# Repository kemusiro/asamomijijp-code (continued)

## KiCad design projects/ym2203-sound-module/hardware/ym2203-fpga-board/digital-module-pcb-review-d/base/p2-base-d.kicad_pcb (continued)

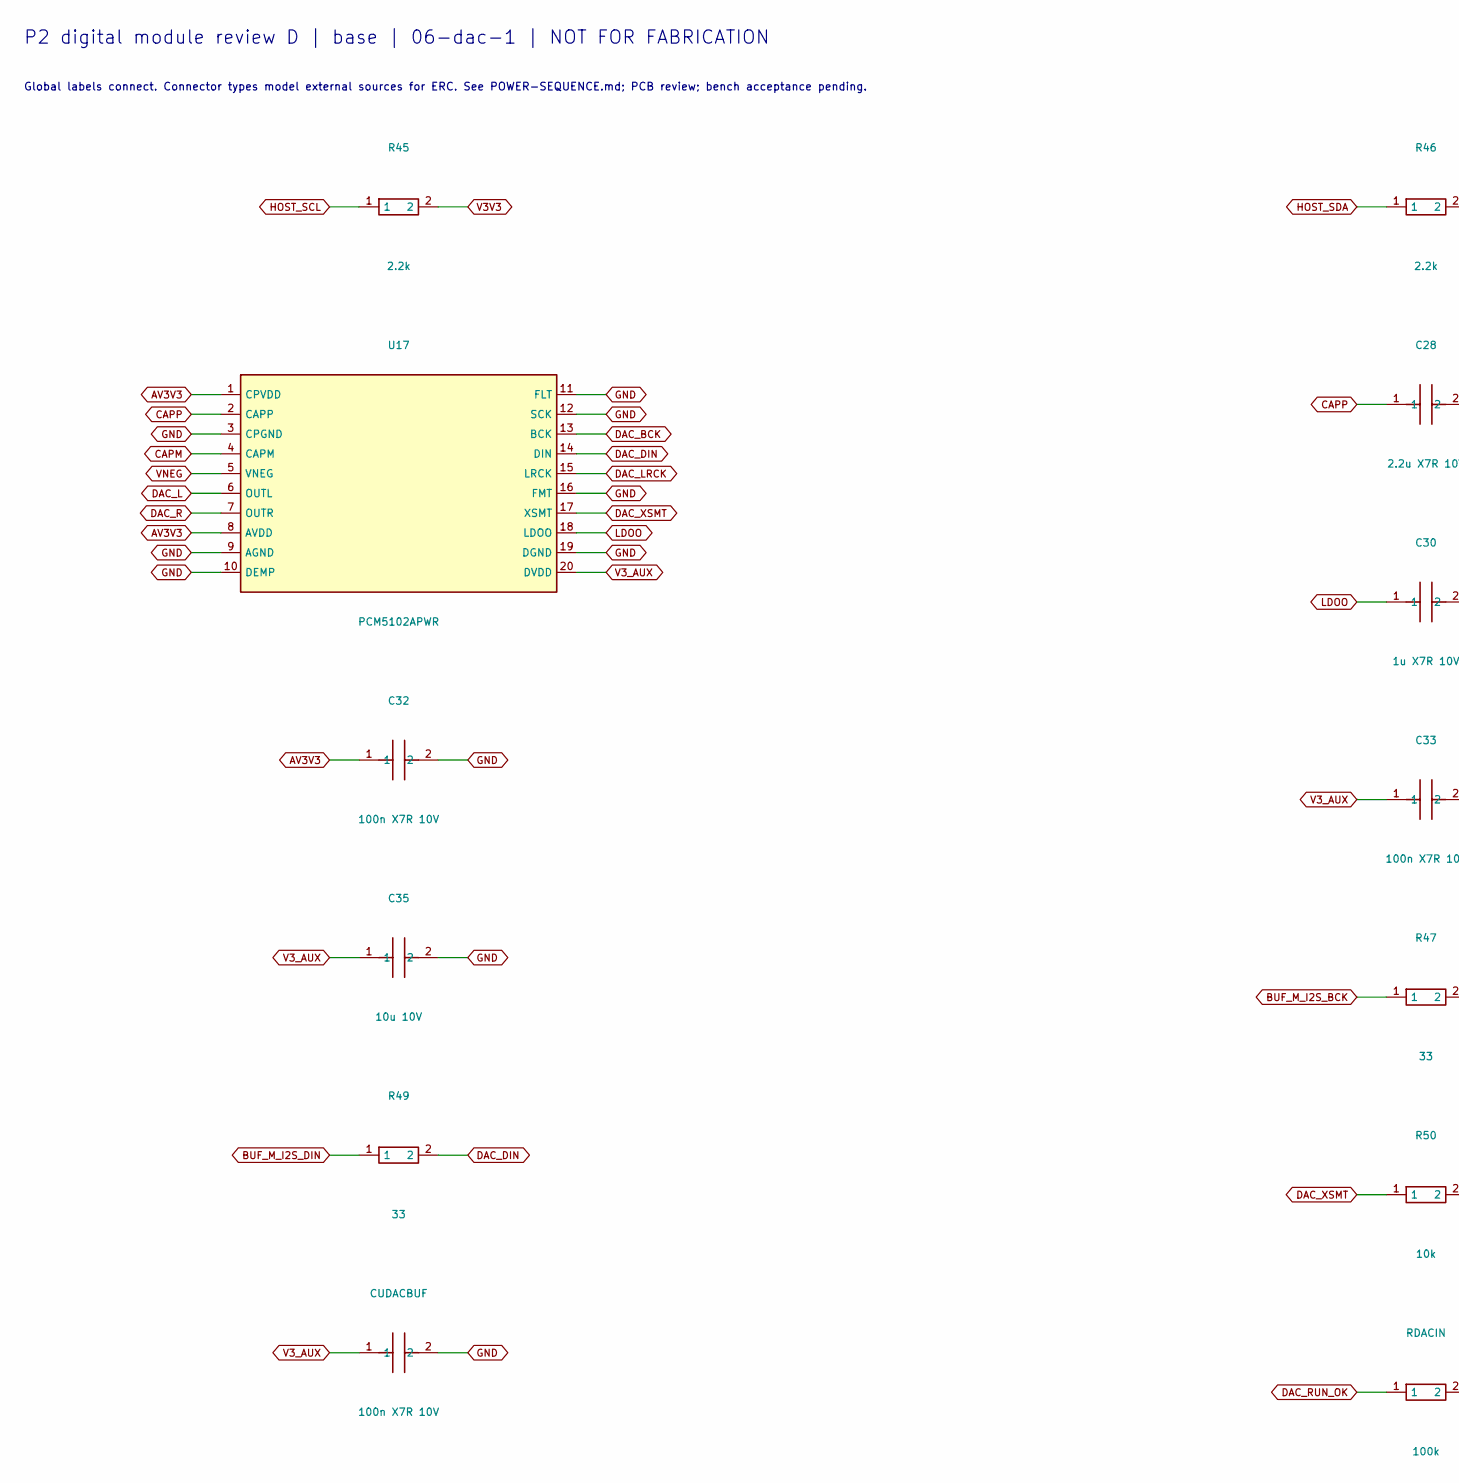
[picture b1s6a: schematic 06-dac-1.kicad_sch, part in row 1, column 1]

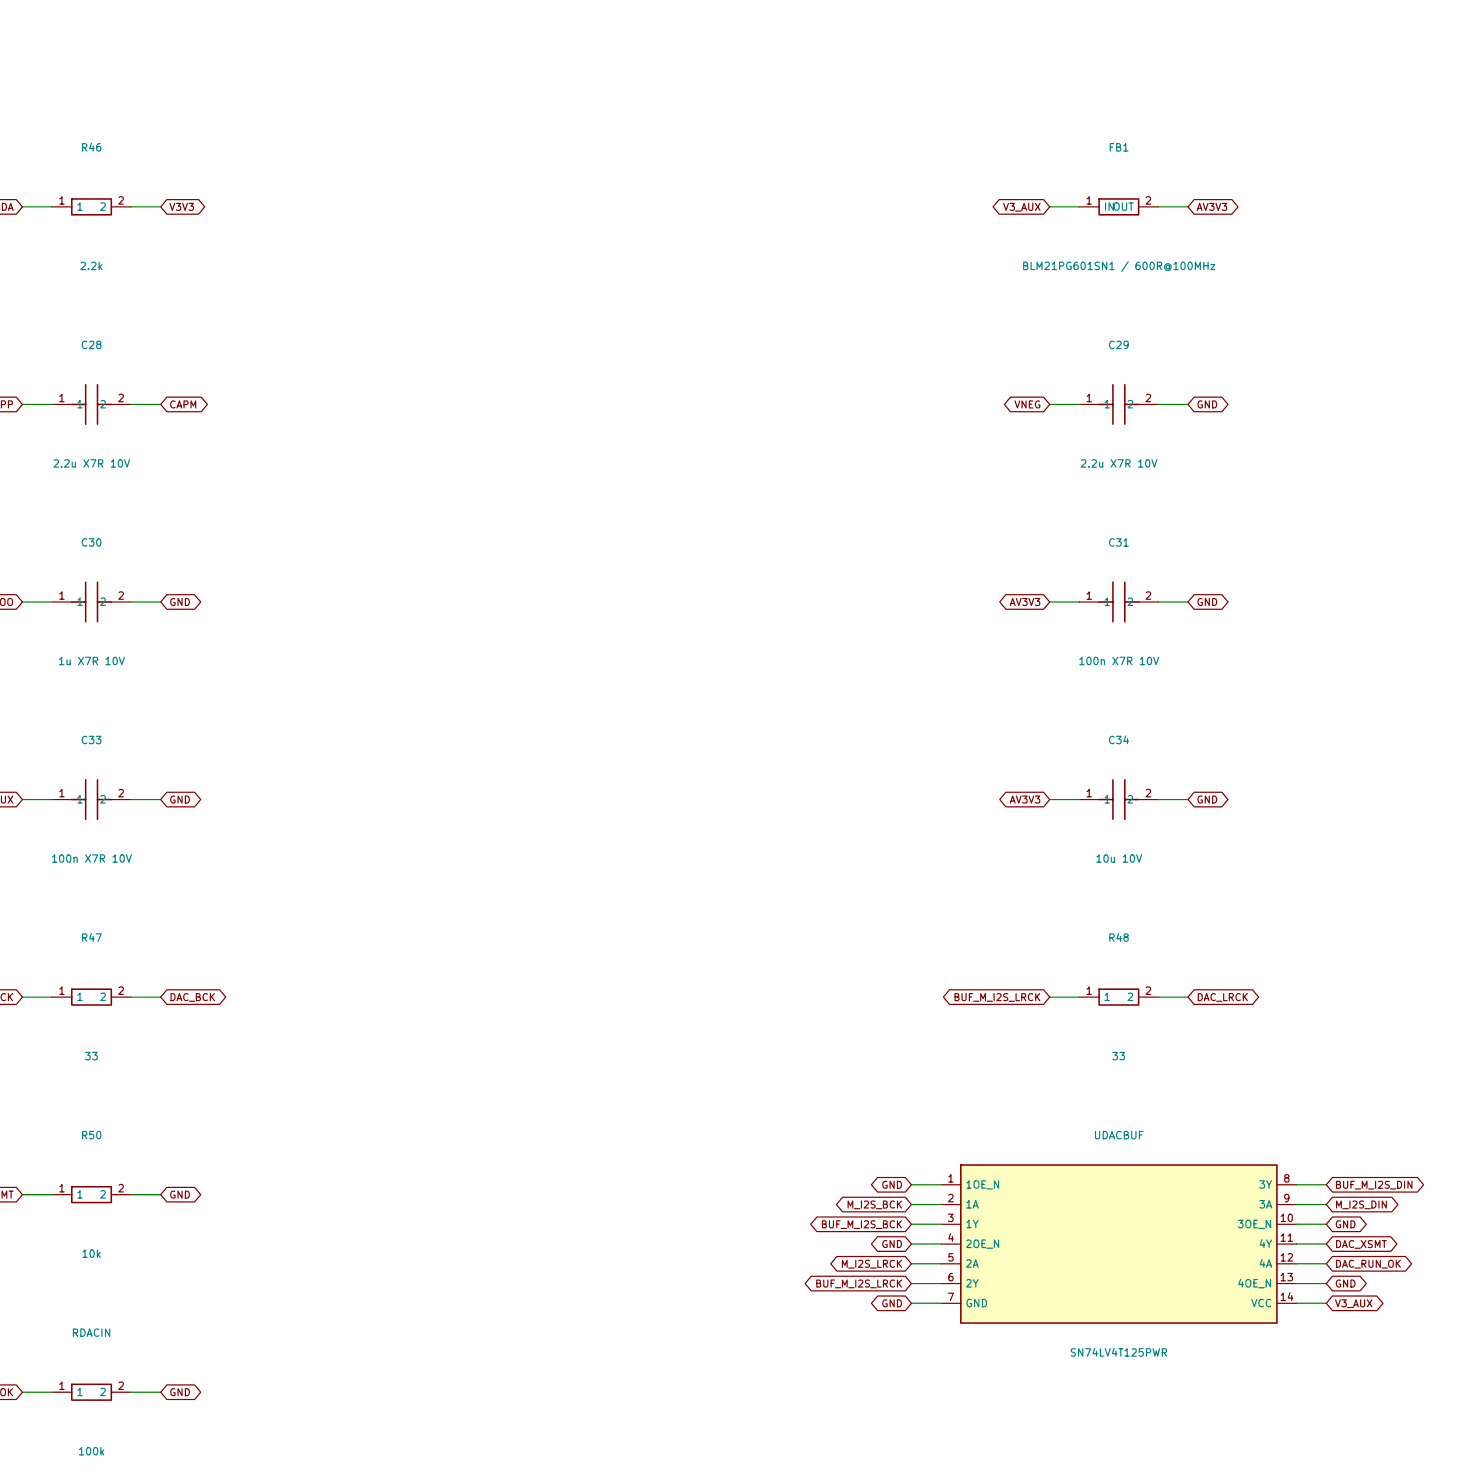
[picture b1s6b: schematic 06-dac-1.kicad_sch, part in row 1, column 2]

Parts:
C28, C29: 2.2u X7R 10V; C_0805_2012Metric
C30: 1u X7R 10V; C_0805_2012Metric
C31, C32, C33: 100n X7R 10V; C_0805_2012Metric
C34, C35: 10u 10V; C_0805_2012Metric
CUDACBUF: 100n X7R 10V; C_0805_2012Metric
FB1: BLM21PG601SN1 / 600R@100MHz; L_0805_2012Metric
R45, R46: 2.2k; R_0805_2012Metric
R47, R48, R49: 33; R_0805_2012Metric
R50: 10k; R_0805_2012Metric
RDACIN: 100k; R_0805_2012Metric
U17: PCM5102APWR; TSSOP-20_4.4x6.5mm_P0.65mm
UDACBUF: SN74LV4T125PWR; TSSOP-14_4.4x5mm_P0.65mm

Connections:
AV3V3: C31.1, C32.1, C34.1, FB1.2 (OUT), U17.1 (CPVDD), U17.8 (AVDD)
BUF_M_I2S_BCK: R47.1, UDACBUF.3 (1Y)
BUF_M_I2S_DIN: R49.1, UDACBUF.8 (3Y)
BUF_M_I2S_LRCK: R48.1, UDACBUF.6 (2Y)
CAPM: C28.2, U17.4 (CAPM)
CAPP: C28.1, U17.2 (CAPP)
DAC_BCK: R47.2, U17.13 (BCK); also elsewhere on the board
DAC_DIN: R49.2, U17.14 (DIN); also elsewhere on the board
DAC_L: U17.6 (OUTL); also elsewhere on the board
DAC_LRCK: R48.2, U17.15 (LRCK); also elsewhere on the board
DAC_R: U17.7 (OUTR); also elsewhere on the board
DAC_RUN_OK: RDACIN.1, UDACBUF.12 (4A); also elsewhere on the board
DAC_XSMT: R50.1, U17.17 (XSMT), UDACBUF.11 (4Y)
GND: C29.2, C30.2, C31.2, C32.2, C33.2, C34.2, C35.2, CUDACBUF.2, R50.2, RDACIN.2, U17.3 (CPGND), U17.9 (AGND), U17.10 (DEMP), U17.11 (FLT), U17.12 (SCK), U17.16 (FMT), U17.19 (DGND), UDACBUF.1 (1OE_N), UDACBUF.4 (2OE_N), UDACBUF.7 (GND), UDACBUF.10 (3OE_N), UDACBUF.13 (4OE_N); also elsewhere on the board
HOST_SCL: R45.1; also elsewhere on the board
HOST_SDA: R46.1; also elsewhere on the board
LDOO: C30.1, U17.18 (LDOO)
M_I2S_BCK: UDACBUF.2 (1A); also elsewhere on the board
M_I2S_DIN: UDACBUF.9 (3A); also elsewhere on the board
M_I2S_LRCK: UDACBUF.5 (2A); also elsewhere on the board
V3V3: R45.2, R46.2; also elsewhere on the board
V3_AUX: C33.1, C35.1, CUDACBUF.1, FB1.1 (IN), U17.20 (DVDD), UDACBUF.14 (VCC); also elsewhere on the board
VNEG: C29.1, U17.5 (VNEG)

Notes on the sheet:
P2 digital module review D | base | 06-dac-1 | NOT FOR FABRICATION
Global labels connect. Connector types model external sources for ERC. See POWER-SEQUENCE.md; PCB review; bench acceptance pending.

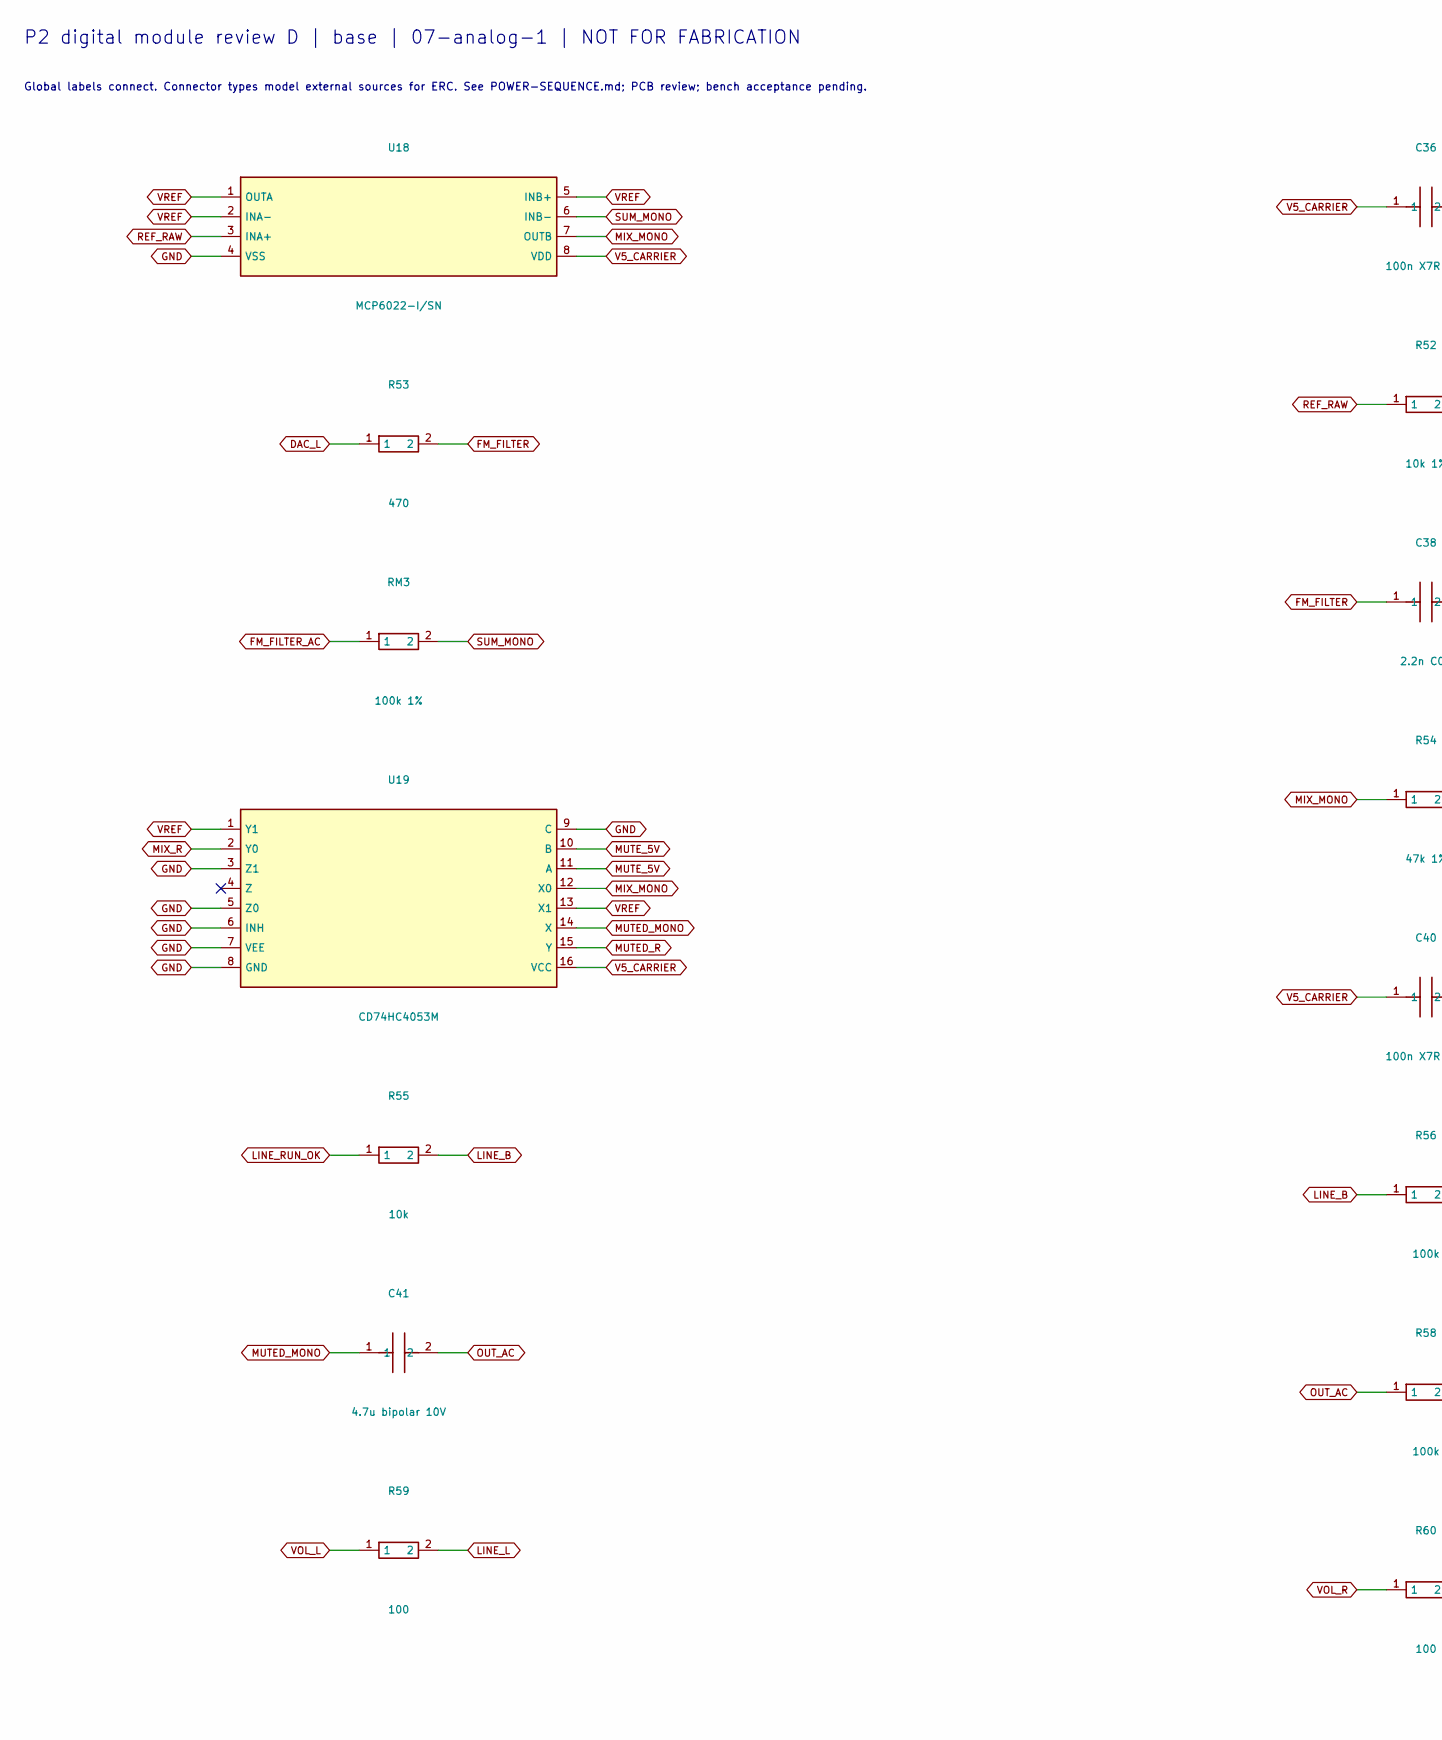
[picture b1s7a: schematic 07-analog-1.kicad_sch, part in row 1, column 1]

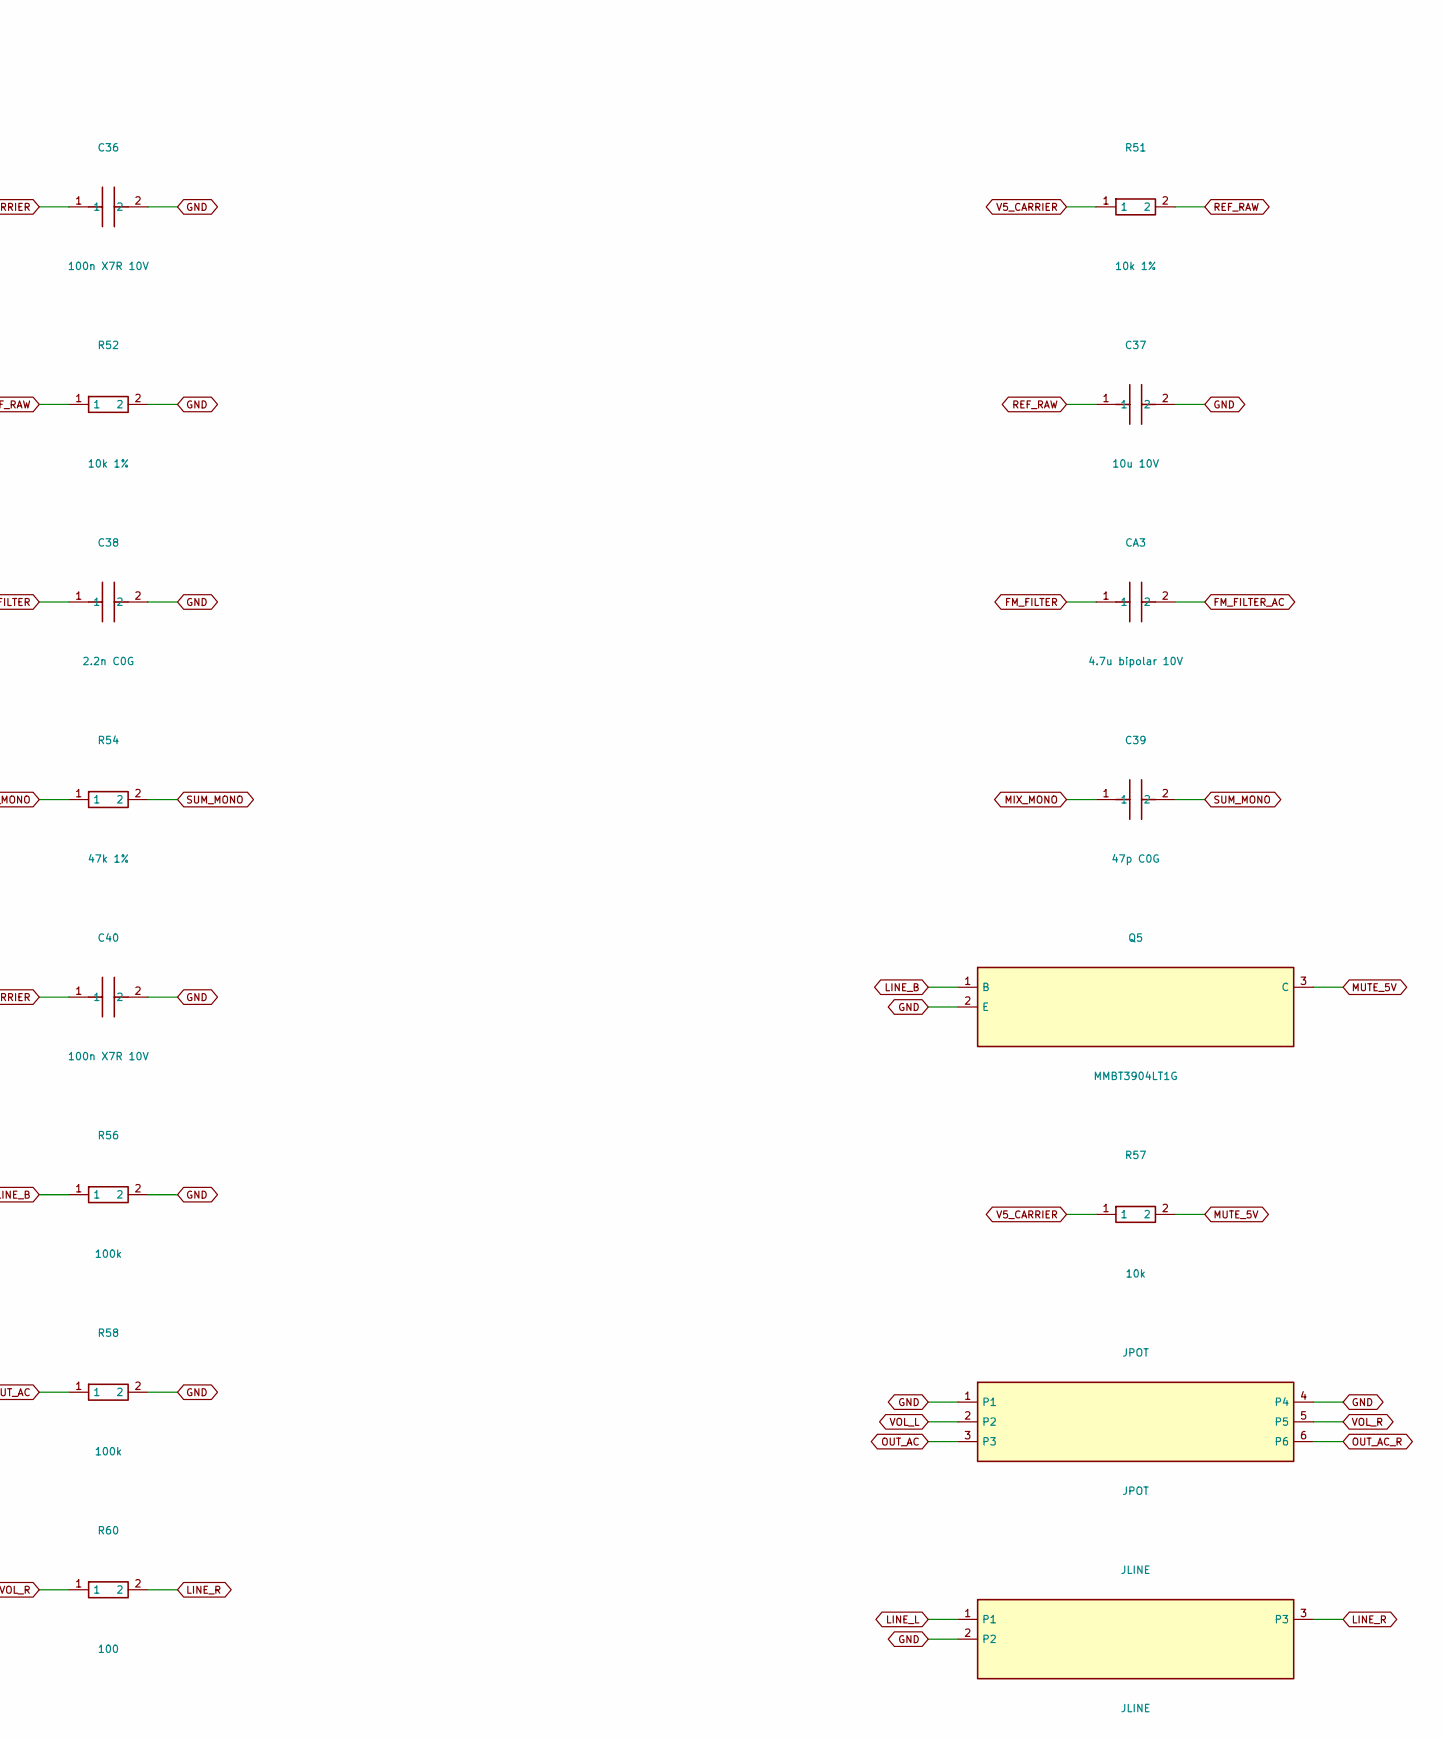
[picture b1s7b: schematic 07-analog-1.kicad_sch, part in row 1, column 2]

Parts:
C36, C40: 100n X7R 10V; C_0805_2012Metric
C37: 10u 10V; C_0805_2012Metric
C38: 2.2n C0G; C_0805_2012Metric
C39: 47p C0G; C_0805_2012Metric
C41: 4.7u bipolar 10V; C_Radial_D5.0mm_H11.0mm_P2.00mm
CA3: 4.7u bipolar 10V; C_Radial_D5.0mm_H11.0mm_P2.00mm
JLINE: JLINE; PinHeader_1x03_P2.54mm_Vertical
JPOT: JPOT; PinHeader_1x06_P2.54mm_Vertical
Q5: MMBT3904LT1G; SOT-23
R51, R52: 10k 1%; R_0805_2012Metric
R53: 470; R_0805_2012Metric
R54: 47k 1%; R_0805_2012Metric
R55, R57: 10k; R_0805_2012Metric
R56, R58: 100k; R_0805_2012Metric
R59, R60: 100; R_0805_2012Metric
RM3: 100k 1%; R_0805_2012Metric
U18: MCP6022-I/SN; SOIC-8_3.9x4.9mm_P1.27mm
U19: CD74HC4053M; SOIC-16_3.9x9.9mm_P1.27mm

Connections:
DAC_L: R53.1; also elsewhere on the board
FM_FILTER: C38.1, CA3.1, R53.2
FM_FILTER_AC: CA3.2, RM3.1
GND: C36.2, C37.2, C38.2, C40.2, JLINE.2, JPOT.1, JPOT.4, Q5.2 (E), R52.2, R56.2, R58.2, U18.4 (VSS), U19.3 (Z1), U19.5 (Z0), U19.6 (INH), U19.7 (VEE), U19.8 (GND), U19.9 (C); also elsewhere on the board
LINE_B: Q5.1 (B), R55.2, R56.1
LINE_L: JLINE.1, R59.2
LINE_R: JLINE.3, R60.2
LINE_RUN_OK: R55.1; also elsewhere on the board
MIX_MONO: C39.1, R54.1, U18.7 (OUTB), U19.12 (X0)
MIX_R: U19.2 (Y0); also elsewhere on the board
MUTED_MONO: C41.1, U19.14 (X)
MUTED_R: U19.15 (Y); also elsewhere on the board
MUTE_5V: Q5.3 (C), R57.2, U19.10 (B), U19.11 (A)
OUT_AC: C41.2, JPOT.3, R58.1
OUT_AC_R: JPOT.6; also elsewhere on the board
REF_RAW: C37.1, R51.2, R52.1, U18.3 (INA+)
SUM_MONO: C39.2, R54.2, RM3.2, U18.6 (INB-)
V5_CARRIER: C36.1, C40.1, R51.1, R57.1, U18.8 (VDD), U19.16 (VCC); also elsewhere on the board
VOL_L: JPOT.2, R59.1
VOL_R: JPOT.5, R60.1
VREF: U18.1 (OUTA), U18.2 (INA-), U18.5 (INB+), U19.1 (Y1), U19.13 (X1); also elsewhere on the board

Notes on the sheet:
P2 digital module review D | base | 07-analog-1 | NOT FOR FABRICATION
Global labels connect. Connector types model external sources for ERC. See POWER-SEQUENCE.md; PCB review; bench acceptance pending.

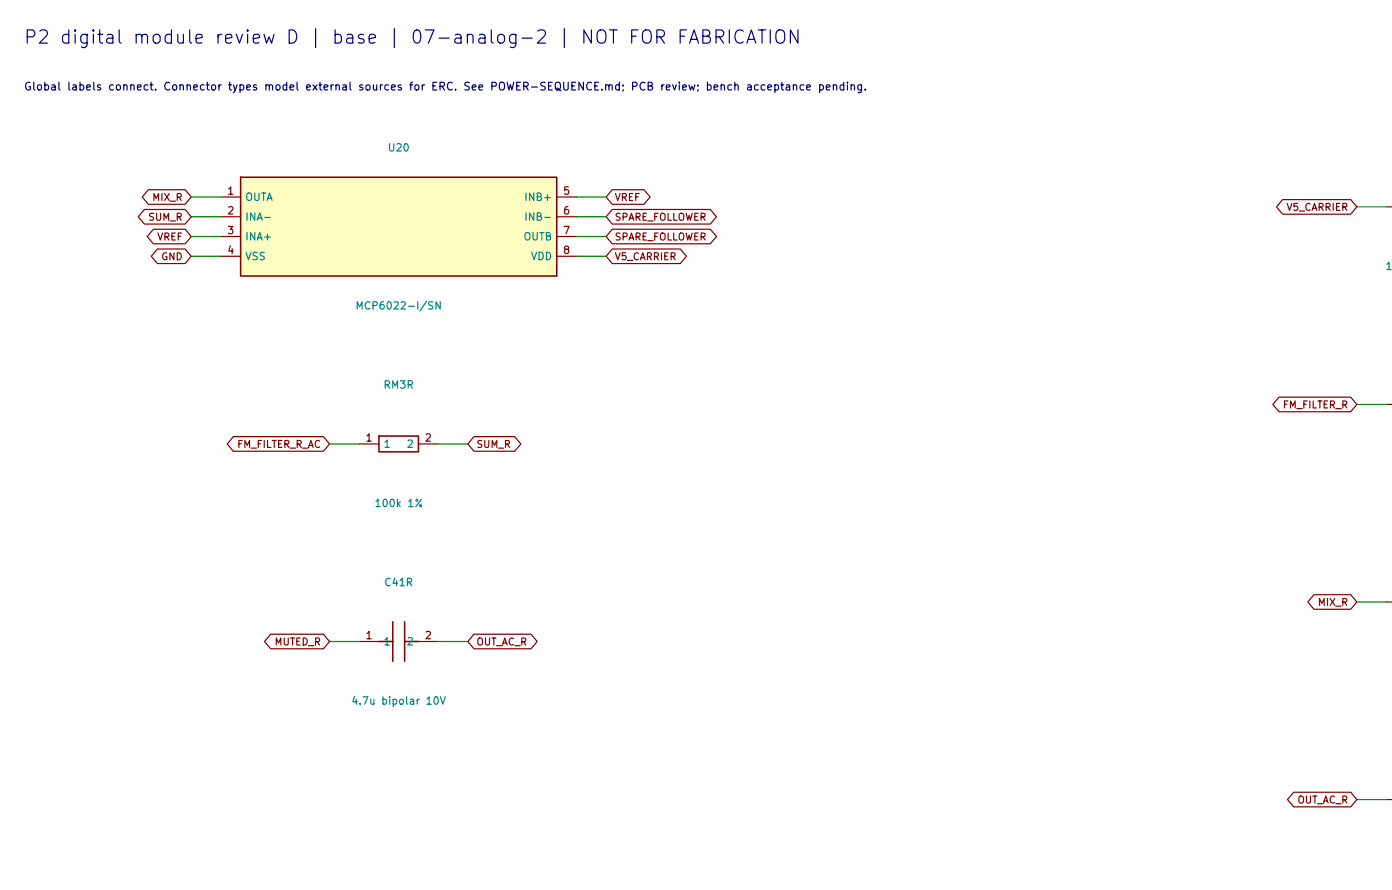
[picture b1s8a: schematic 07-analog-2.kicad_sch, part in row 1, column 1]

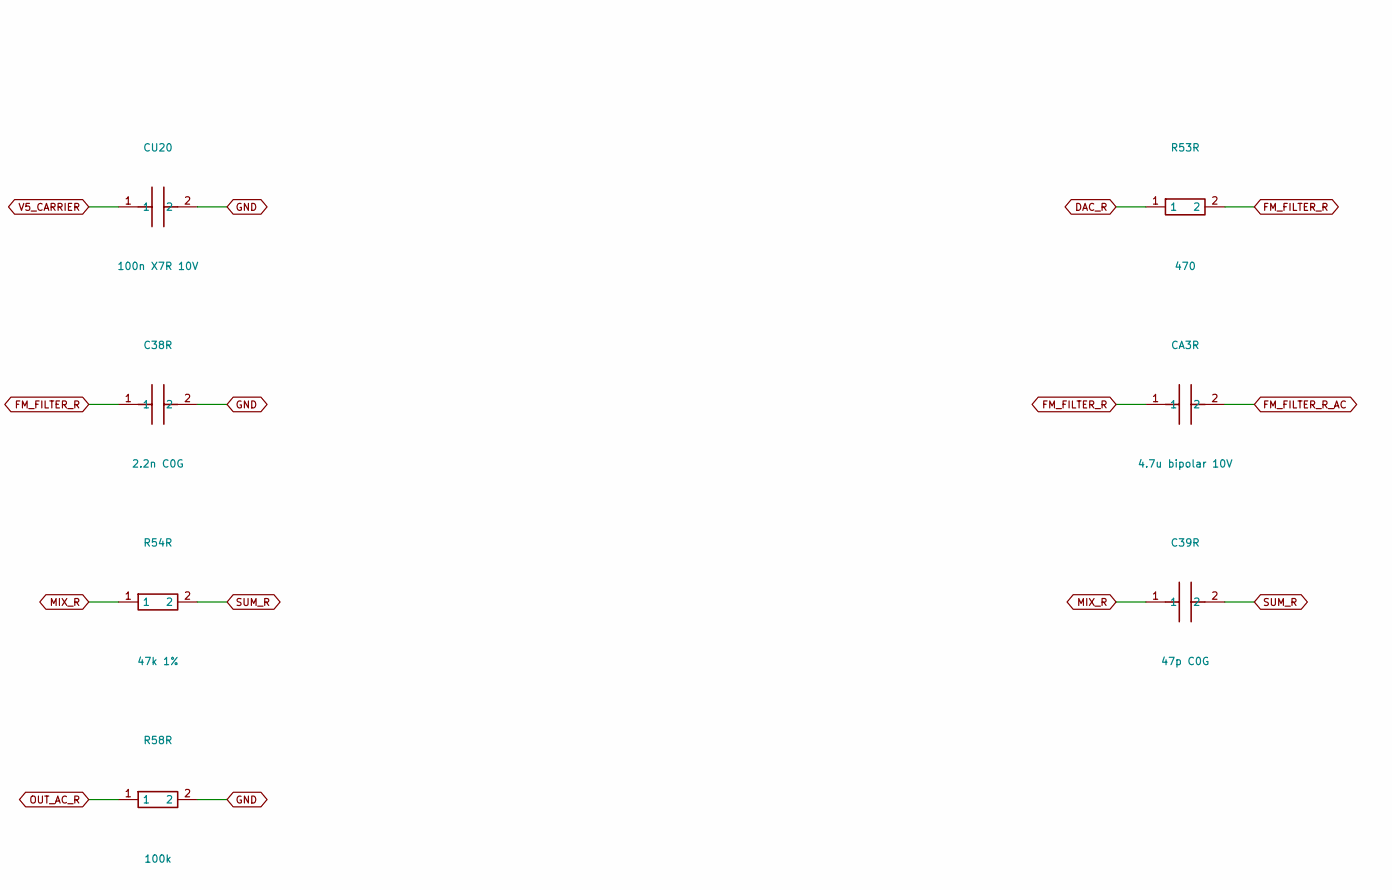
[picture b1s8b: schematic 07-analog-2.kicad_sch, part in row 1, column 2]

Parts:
C38R: 2.2n C0G; C_0805_2012Metric
C39R: 47p C0G; C_0805_2012Metric
C41R: 4.7u bipolar 10V; C_Radial_D5.0mm_H11.0mm_P2.00mm
CA3R: 4.7u bipolar 10V; C_Radial_D5.0mm_H11.0mm_P2.00mm
CU20: 100n X7R 10V; C_0805_2012Metric
R53R: 470; R_0805_2012Metric
R54R: 47k 1%; R_0805_2012Metric
R58R: 100k; R_0805_2012Metric
RM3R: 100k 1%; R_0805_2012Metric
U20: MCP6022-I/SN; SOIC-8_3.9x4.9mm_P1.27mm

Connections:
DAC_R: R53R.1; also elsewhere on the board
FM_FILTER_R: C38R.1, CA3R.1, R53R.2
FM_FILTER_R_AC: CA3R.2, RM3R.1
GND: C38R.2, CU20.2, R58R.2, U20.4 (VSS); also elsewhere on the board
MIX_R: C39R.1, R54R.1, U20.1 (OUTA); also elsewhere on the board
MUTED_R: C41R.1; also elsewhere on the board
OUT_AC_R: C41R.2, R58R.1; also elsewhere on the board
SPARE_FOLLOWER: U20.6 (INB-), U20.7 (OUTB)
SUM_R: C39R.2, R54R.2, RM3R.2, U20.2 (INA-)
V5_CARRIER: CU20.1, U20.8 (VDD); also elsewhere on the board
VREF: U20.3 (INA+), U20.5 (INB+); also elsewhere on the board

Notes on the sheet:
P2 digital module review D | base | 07-analog-2 | NOT FOR FABRICATION
Global labels connect. Connector types model external sources for ERC. See POWER-SEQUENCE.md; PCB review; bench acceptance pending.

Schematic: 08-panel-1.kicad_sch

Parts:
CPANEL: 100n X7R 10V; C_0805_2012Metric
DLED0: RX GREEN; LED_D3.0mm
DLED1: FM1; LED_D3.0mm
DLED2: FM2; LED_D3.0mm
DLED3: FM3; LED_D3.0mm
DLED4: SSGA; LED_D3.0mm
DLED5: SSGB; LED_D3.0mm
RLED0, RLED1, RLED2, RLED3, RLED4, RLED5: 1k; R_0805_2012Metric
RP0, RP1, RP2, RP3, RP4, RP5: 10k; R_0805_2012Metric
SWCLOCK: 4-bit DIP ON=0 SW1=LSB; SW_DIP_SPSTx04_Slide_6.7x11.72mm_W7.62mm_P2.54mm_LowProfile
SWSTOP: STOP; SW_PUSH_6mm_H4.3mm
SWTEST: TEST; SW_PUSH_6mm_H4.3mm
UPANEL: MCP23017-E/SO; SOIC-28W_7.5x17.9mm_P1.27mm

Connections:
DIP1_N: RP0.2, SWCLOCK.1 (SW1), UPANEL.21 (GPA0)
DIP2_N: RP1.2, SWCLOCK.2 (SW2), UPANEL.22 (GPA1)
DIP3_N: RP2.2, SWCLOCK.3 (SW3), UPANEL.23 (GPA2)
DIP4_N: RP3.2, SWCLOCK.4 (SW4), UPANEL.24 (GPA3)
FM1_LED_N: DLED1.1 (K), UPANEL.1 (GPB0)
FM2_LED_N: DLED2.1 (K), UPANEL.2 (GPB1)
FM3_LED_N: DLED3.1 (K), UPANEL.3 (GPB2)
GND: CPANEL.2, SWCLOCK.5 (GND), SWCLOCK.6 (GND), SWCLOCK.7 (GND), SWCLOCK.8 (GND), SWSTOP.2 (B), SWTEST.2 (B), UPANEL.10 (VSS), UPANEL.15 (A0), UPANEL.16 (A1), UPANEL.17 (A2); also elsewhere on the board
LED_ANODE0: DLED0.2 (A), RLED0.1
LED_ANODE1: DLED1.2 (A), RLED1.1
LED_ANODE2: DLED2.2 (A), RLED2.1
LED_ANODE3: DLED3.2 (A), RLED3.1
LED_ANODE4: DLED4.2 (A), RLED4.1
LED_ANODE5: DLED5.2 (A), RLED5.1
PANEL_SCL: UPANEL.12 (SCL); also elsewhere on the board
PANEL_SDA: UPANEL.13 (SDA); also elsewhere on the board
RUN_N: UPANEL.18 (RESETn); also elsewhere on the board
RX_LED_N: DLED0.1 (K), UPANEL.28 (GPA7)
SSGA_LED_N: DLED4.1 (K), UPANEL.4 (GPB3)
SSGB_LED_N: DLED5.1 (K), UPANEL.5 (GPB4)
SSGC_LED_N: UPANEL.6 (GPB5); also elsewhere on the board
STOP_N: RP4.2, SWSTOP.1 (A), UPANEL.25 (GPA4)
TEST_N: RP5.2, SWTEST.1 (A), UPANEL.26 (GPA5)
V3V3: CPANEL.1, RLED0.2, RLED1.2, RLED2.2, RLED3.2, RLED4.2, RLED5.2, RP0.1, RP1.1, RP2.1, RP3.1, RP4.1, RP5.1, UPANEL.9 (VDD); also elsewhere on the board

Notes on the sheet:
P2 digital module review D | base | 08-panel-1 | NOT FOR FABRICATION
Global labels connect. Connector types model external sources for ERC. See POWER-SEQUENCE.md; PCB review; bench acceptance pending.

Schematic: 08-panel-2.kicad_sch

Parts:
DLED6: SSGC; LED_D3.0mm
RLED6: 1k; R_0805_2012Metric

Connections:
LED_ANODE6: DLED6.2 (A), RLED6.1
SSGC_LED_N: DLED6.1 (K); also elsewhere on the board
V3V3: RLED6.2; also elsewhere on the board

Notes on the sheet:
P2 digital module review D | base | 08-panel-2 | NOT FOR FABRICATION
Global labels connect. Connector types model external sources for ERC. See POWER-SEQUENCE.md; PCB review; bench acceptance pending.

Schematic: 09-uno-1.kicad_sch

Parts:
JP5V: OPEN DEFAULT / SHIELD POWER; SolderJumper-2_P1.3mm_Open_RoundedPad1.0x1.5mm
JP_SCL: CLOSED I2C / OPEN ADC (STOPPED); SolderJumper-2_P1.3mm_Bridged_RoundedPad1.0x1.5mm
JP_SDA: CLOSED I2C / OPEN ADC (STOPPED); SolderJumper-2_P1.3mm_Bridged_RoundedPad1.0x1.5mm
JUNO_A: JUNO_A 3V3 ONLY; JUNO_A
JUNO_D0: JUNO_D0 3V3 ONLY; JUNO_D0
JUNO_D8: JUNO_D8 3V3 ONLY; JUNO_D8
JUNO_PWR: JUNO_PWR 3V3 ONLY; JUNO_PWR
JUNO_SPI: JUNO_SPI 3V3 ONLY; JUNO_SPI

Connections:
EXT_A0: JUNO_A.1 (A0); also elsewhere on the board
EXT_A1: JUNO_A.2 (A1); also elsewhere on the board
EXT_A2: JUNO_A.3 (A2); also elsewhere on the board
EXT_A3: JUNO_A.4 (A3); also elsewhere on the board
EXT_A4: JP_SDA.1 (MCU_HEADER), JUNO_A.5 (A4), JUNO_D8.9 (SDA); also elsewhere on the board
EXT_A5: JP_SCL.1 (MCU_HEADER), JUNO_A.6 (A5), JUNO_D8.10 (SCL); also elsewhere on the board
EXT_D0: JUNO_D0.1 (D0); also elsewhere on the board
EXT_D1: JUNO_D0.2 (D1); also elsewhere on the board
EXT_D2: JUNO_D0.3 (D2); also elsewhere on the board
EXT_D3: JUNO_D0.4 (D3); also elsewhere on the board
EXT_D4: JUNO_D0.5 (D4); also elsewhere on the board
EXT_D5: JUNO_D0.6 (D5); also elsewhere on the board
EXT_D6: JUNO_D0.7 (D6); also elsewhere on the board
EXT_D7: JUNO_D0.8 (D7); also elsewhere on the board
EXT_D8: JUNO_D8.1 (D8); also elsewhere on the board
EXT_D9: JUNO_D8.2 (D9); also elsewhere on the board
EXT_D10: JUNO_D8.3 (D10); also elsewhere on the board
EXT_D11: JUNO_D8.4 (D11), JUNO_SPI.4 (COPI); also elsewhere on the board
EXT_D12: JUNO_D8.5 (D12), JUNO_SPI.1 (CIPO); also elsewhere on the board
EXT_D13: JUNO_D8.6 (D13), JUNO_SPI.3 (SCK); also elsewhere on the board
GND: JUNO_D8.7 (GND), JUNO_PWR.6 (GND), JUNO_PWR.7 (GND), JUNO_SPI.6 (GND); also elsewhere on the board
PANEL_SCL: JP_SCL.2 (BOARD_I2C); also elsewhere on the board
PANEL_SDA: JP_SDA.2 (BOARD_I2C); also elsewhere on the board
RUN_N: JUNO_PWR.3 (RESET), JUNO_SPI.5 (RESET); also elsewhere on the board
SHIELD_5V: JP5V.2 (SHIELD), JUNO_PWR.5 (5V)
V3V3: JUNO_PWR.2 (IOREF), JUNO_SPI.2 (VCC_3V3); also elsewhere on the board
V3_AUX: JUNO_PWR.4 (3V3); also elsewhere on the board
V5_CARRIER: JP5V.1 (5V); also elsewhere on the board

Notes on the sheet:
P2 digital module review D | base | 09-uno-1 | NOT FOR FABRICATION
Global labels connect. Connector types model external sources for ERC. See POWER-SEQUENCE.md; PCB review; bench acceptance pending.

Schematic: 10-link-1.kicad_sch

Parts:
CURXBUF: 100n X7R 10V; C_0805_2012Metric
JMOD: P2 DIGITAL 32 / pin32 KEY; PinSocket_2x16_P2.54mm_Vertical
RALERT: 0; R_0805_2012Metric
RBALERT: 10k; R_0805_2012Metric
RBCS: 10k; R_0805_2012Metric
RBEN: 10k; R_0805_2012Metric
RBI0, RBI1: 100k; R_0805_2012Metric
RBMISO: 100k; R_0805_2012Metric
RBSD: 100k; R_0805_2012Metric
RLKBCK: 33; R_0805_2012Metric
RLKCS: 33; R_0805_2012Metric
RLKEN: 33; R_0805_2012Metric
RLKLR: 33; R_0805_2012Metric
RLKMOSI: 33; R_0805_2012Metric
RLKSCK: 33; R_0805_2012Metric
URXBUF: SN74LV4T125PWR; TSSOP-14_4.4x5mm_P0.65mm

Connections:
GND: CURXBUF.2, JMOD.2 (GND), JMOD.4 (GND), JMOD.6 (GND), JMOD.10 (GND), JMOD.14 (GND), JMOD.16 (GND), JMOD.18 (GND), JMOD.20 (GND), JMOD.22 (GND), JMOD.24 (GND), JMOD.26 (GND), JMOD.31 (GND), RBEN.2, RBI0.2, RBI1.2, RBMISO.2, RBSD.2, URXBUF.4 (2OE_N), URXBUF.7 (GND), URXBUF.9 (3A), URXBUF.12 (4A); also elsewhere on the board
L_MOD_ALERT_N: JMOD.12 (MOD_ALERT_N), RALERT.1, RBALERT.1
L_MOD_ENABLE: JMOD.11 (MOD_ENABLE), RLKEN.2
L_MOD_I2S_BCK: JMOD.13 (MOD_I2S_BCK), RLKBCK.2
L_MOD_I2S_DATA: JMOD.17 (MOD_I2S_DATA), RBI1.1, URXBUF.5 (2A)
L_MOD_I2S_LRCK: JMOD.15 (MOD_I2S_LRCK), RLKLR.2
L_MOD_SPI_CS_N: JMOD.9 (MOD_SPI_CS_N), RLKCS.2
L_MOD_SPI_MISO: JMOD.8 (MOD_SPI_MISO), RBI0.1, URXBUF.2 (1A)
L_MOD_SPI_MOSI: JMOD.7 (MOD_SPI_MOSI), RLKMOSI.2
L_MOD_SPI_SCK: JMOD.5 (MOD_SPI_SCK), RLKSCK.2
L_SOUND_CLK0: JMOD.19 (SOUND_CLK0); also elsewhere on the board
L_SOUND_CLK1: JMOD.21 (SOUND_CLK1); also elsewhere on the board
L_SOUND_CLK2: JMOD.23 (SOUND_CLK2); also elsewhere on the board
MODULE_PERMIT: RLKEN.1; also elsewhere on the board
MOD_ALERT_N: RALERT.2; also elsewhere on the board
MOD_ENABLE: RBEN.1; also elsewhere on the board
MOD_I2S_DATA: RBSD.1, URXBUF.6 (2Y); also elsewhere on the board
MOD_SPI_CS_N: RBCS.1, RLKCS.1, URXBUF.1 (1OE_N); also elsewhere on the board
MOD_SPI_MISO: RBMISO.1, URXBUF.3 (1Y); also elsewhere on the board
MOD_SPI_MOSI: RLKMOSI.1; also elsewhere on the board
MOD_SPI_SCK: RLKSCK.1; also elsewhere on the board
M_I2S_BCK: RLKBCK.1; also elsewhere on the board
M_I2S_LRCK: RLKLR.1; also elsewhere on the board
V3V3: CURXBUF.1, RBALERT.2, RBCS.2, URXBUF.10 (3OE_N), URXBUF.13 (4OE_N), URXBUF.14 (VCC); also elsewhere on the board
V5_CARRIER: JMOD.1 (V5_MODULE), JMOD.3 (V5_MODULE); also elsewhere on the board

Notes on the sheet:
P2 digital module review D | base | 10-link-1 | NOT FOR FABRICATION
Global labels connect. Connector types model external sources for ERC. See POWER-SEQUENCE.md; PCB review; bench acceptance pending.
